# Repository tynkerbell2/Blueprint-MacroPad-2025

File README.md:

# Blueprint-MacroPad-2025

## **This is a general overview**

A personal micropad with capabilities to make custom binds with hotswappable 3d printed caps for flare. Mainly used for listening to music or lots of copy and pasting. Able to add profiles in code to customize buttons.  

List of parts availibe on the BOM

## **Schematic**

This was the schematic created for this project

## **PCB**

PCB looking fire with the scorpian     

## **DXF for the keyboard**

## **Creating the 3d models**

This is case, made sure that everything fit and even had a little wiggle room. Also added a cool caligraphic W for my name - Will  

## **Code**

And this was the code that took me forever to do, I definitely overcomplicated this part but I must say I am very proud of it. Next project I might even try to incorperate some sort of app that would interface with the micro-controller if possible and say what song is playing or the current volume - right now the volume is just a guess. No clue if any of this code even works, haven't really had the chance to try it

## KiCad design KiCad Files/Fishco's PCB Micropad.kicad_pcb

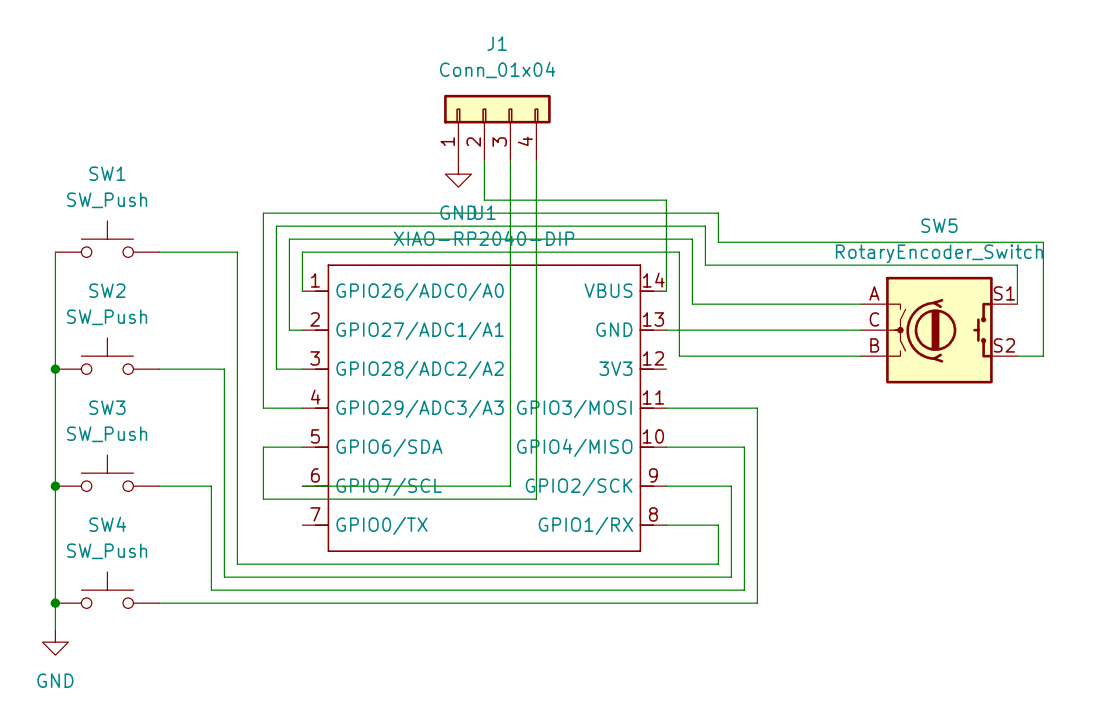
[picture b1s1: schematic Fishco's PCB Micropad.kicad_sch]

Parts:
J1: Conn_01x04; SSD1306-0.91-OLED-4pin-128x32
SW1, SW2, SW3, SW4: SW_Push; SW_Cherry_MX_1.00u_PCB
SW5: RotaryEncoder_Switch; RotaryEncoder_Alps_EC11E-Switch_Vertical_H20mm
U1: XIAO-RP2040-DIP

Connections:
GND: J1.1, SW1.1, SW2.1, SW3.1, SW4.1
unnamed: J1.2, U1.14 (VBUS)
unnamed: J1.3, U1.6 (GPIO7/SCL)
unnamed: J1.4, U1.5 (GPIO6/SDA)
unnamed: SW5.C, U1.13 (GND)
unnamed: SW1.2, U1.8 (GPIO1/RX)
unnamed: SW2.2, U1.9 (GPIO2/SCK)
unnamed: SW4.2, U1.11 (GPIO3/MOSI)
unnamed: SW3.2, U1.10 (GPIO4/MISO)
unnamed: SW5.B, U1.1 (GPIO26/ADC0/A0)
unnamed: SW5.A, U1.2 (GPIO27/ADC1/A1)
unnamed: SW5.S1, U1.3 (GPIO28/ADC2/A2)
unnamed: SW5.S2, U1.4 (GPIO29/ADC3/A3)

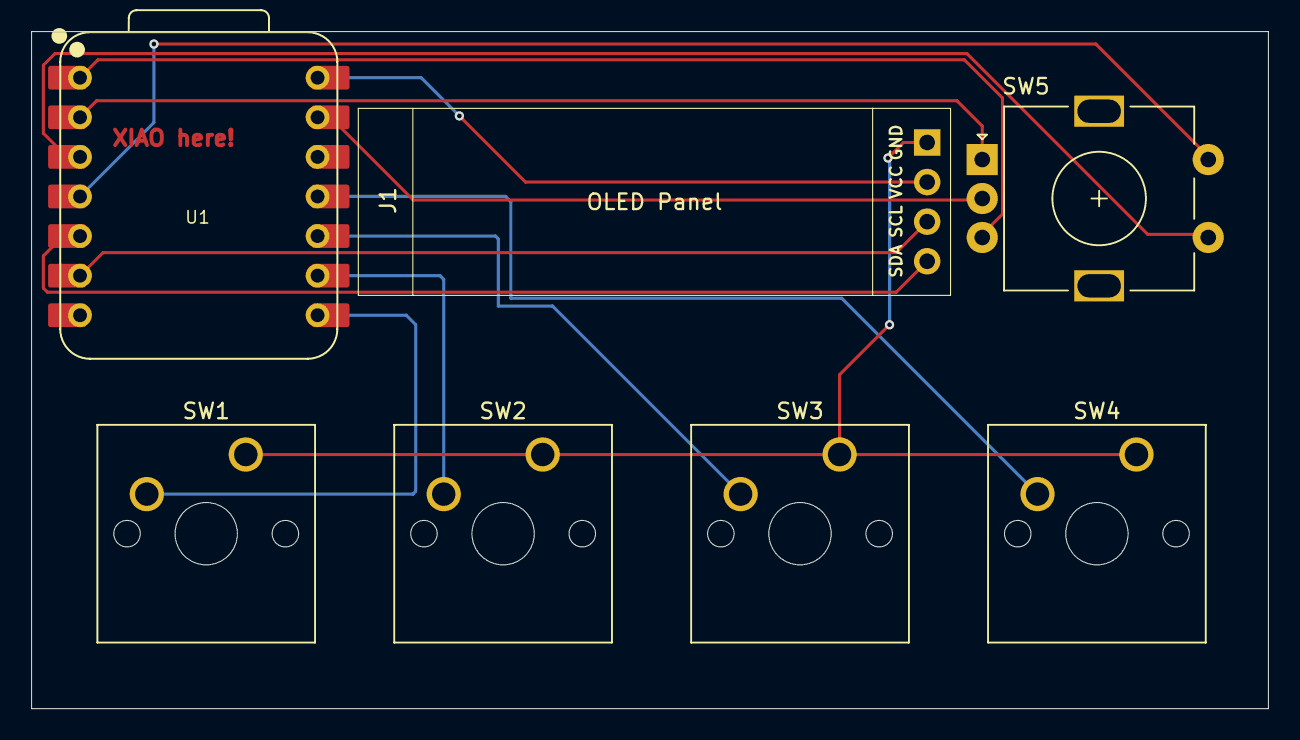
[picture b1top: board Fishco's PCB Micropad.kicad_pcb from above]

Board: 2 copper layers, 79.4 x 43.4 mm, 7 parts (0 on the bottom side), 13 nets.

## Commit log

2025-12-10 Enhance README with images and project details
    Added images and descriptions of the PCB and case design, along with notes on the code complexity and future project ideas.
2025-12-10 Add keyboard functionality with OLED and encoder
    Implement keyboard with I2C OLED display and rotary encoder support.
2025-12-11 Update README with new image and project details
    Added a new image to the README and updated project description.
2025-12-11 Add list of parts to README
    Added a list of parts used in the Blueprint-MacroPad-2025 project.
2025-12-11 Fix formatting and update section headers in README
2025-12-11 Rename Fishco's PCB Micropad.kicad_pcb to Code/Fishco's PCB Micropad.kicad_pcb
2025-12-11 Rename Fishco's PCB Micropad.kicad_pcb to Fishco's PCB Micropad.kicad_pcb
2025-12-11 Rename Fishco's PCB Micropad.kicad_pro to KiCad Files/Fishco's PCB Micropad.kicad_pro
2025-12-11 Rename Fishco's PCB Micropad.kicad_sch to KiCad Files/Fishco's PCB Micropad.kicad_sch
2025-12-11 Rename Case Bottom.stl to 3d Models/Case Bottom.stl
2025-12-11 Rename MacroPad Top Plate.stl to 3d Models/MacroPad Top Plate.stl
2025-12-11 Create Photo Gallery
2025-12-11 Add images to Photo Gallery
    Added multiple images to the Photo Gallery section.
2025-12-11 Remove duplicate image entries in Photo Gallery
2025-12-11 Update image source in Photo Gallery
2025-12-11 Update Photo Gallery with new images
    Added multiple images to the photo gallery.
2025-12-11 Add BOM.csv with component list
2025-12-11 Add overview section to README
    Added a general overview section to the README.
2025-12-11 Update README with project overview and parts list
    Added a brief overview of the project and its purpose.
2025-12-11 Fix formatting in README overview section
    Fixed formatting issue in README.md.
2025-12-11 Change header level in README overview
2025-12-11 Enhance README with additional project details
    Updated the README.md to include new sections and images for schematic, PCB, DXF, 3D models, and code. Improved formatting and descriptions for clarity.
2025-12-11 Fix formatting and text in README.md
    Corrected formatting issues in PCB section and improved text clarity.
2025-12-11 Fix formatting of PCB description in README
2025-12-11 Fix formatting issue in PCB section of README
2025-12-11 Update README for clarity and typo corrections
    Corrected typos and improved clarity in the README.
2026-01-07 Simplify keyboard initialization and remove comments
    Refactor keyboard setup and remove unused display code.
2026-04-17 Refactor button handling and OLED setup
    Refactor code to improve button handling and OLED display initialization. Remove unused imports and code related to keyboard extensions.
2026-04-17 Revise project status and fix input handling
    Updated project status and fixed input handling for buttons and encoder.
